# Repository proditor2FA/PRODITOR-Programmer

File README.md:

# PRODITOR-Programmer

https://www.proditor.de

Programmer to flash the HOTP firmware and set the HEX secret build with [KiCAD](https://www.kicad.org/) [free-DAP](https://github.com/ataradov/free-dap) and [openOCD](https://openocd.org/).

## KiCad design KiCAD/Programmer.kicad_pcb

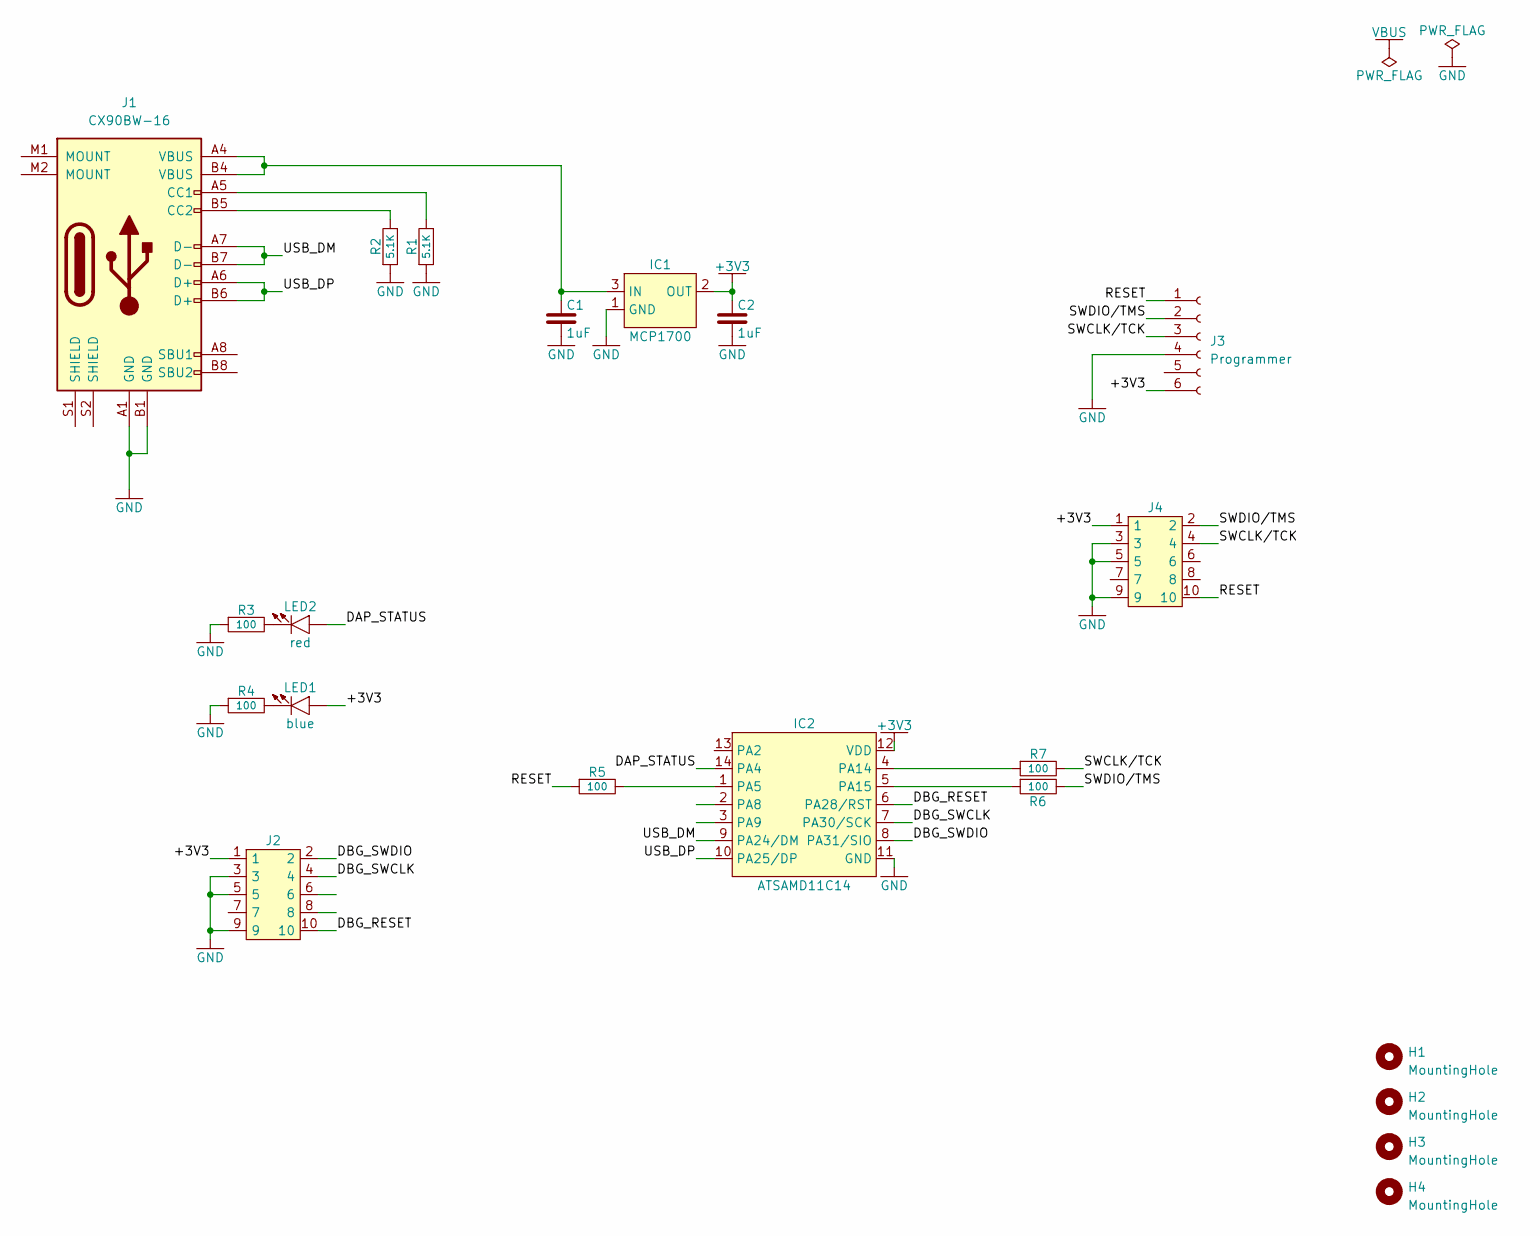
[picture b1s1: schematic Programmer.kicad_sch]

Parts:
C1, C2: 1uF; R_0603_1608Metric_Pad0.98x0.95mm_HandSolder
H1, H2, H3, H4: MountingHole; MountingHole_3.2mm_M3
IC1: MCP1700; SOT-23
IC2: ATSAMD11C14; SOIC-14_3.9x8.7mm_P1.27mm
J1: CX90BW-16; CX90BW-16P
J2, J4: Conn-5x2; Debug_2x05_P1.27mm_Vertical
J3: Programmer; PinHeader_1x06_P1.27mm_Vertical
LED1: blue; R_0603_1608Metric_Pad0.98x0.95mm_HandSolder
LED2: red; R_0603_1608Metric_Pad0.98x0.95mm_HandSolder
R1, R2: 5.1K; R_0603_1608Metric_Pad0.98x0.95mm_HandSolder
R3, R4, R5, R6, R7: 100; R_0603_1608Metric_Pad0.98x0.95mm_HandSolder

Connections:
+3V3: C2.2, IC1.2 (OUT), IC2.12 (VDD), J2.1, J3.6, J4.1, LED1.1 (A)
/DAP_STATUS: IC2.14 (PA4), LED2.1 (A)
/DBG_RESET: IC2.6 (PA28/RST), J2.10
/DBG_SWCLK: IC2.7 (PA30/SCK), J2.4
/DBG_SWDIO: IC2.8 (PA31/SIO), J2.2
/RESET: J3.1, J4.10, R5.1
/SWCLK/TCK: J3.3, J4.4, R7.2
/SWDIO/TMS: J3.2, J4.2, R6.2
/USB_DM: IC2.9 (PA24/DM), J1.A7 (D-), J1.B7 (D-)
/USB_DP: IC2.10 (PA25/DP), J1.A6 (D+), J1.B6 (D+)
GND: C1.1, C2.1, IC1.1 (GND), IC2.11 (GND), J1.A1 (GND), J1.B1 (GND), J2.3, J2.5, J2.9, J3.4, J4.3, J4.5, J4.9, R1.1, R2.1, R3.1, R4.1
unnamed: C1.2, IC1.3 (IN), J1.A4 (VBUS), J1.B4 (VBUS)
unnamed: IC2.1 (PA5), R5.2
unnamed: IC2.4 (PA14), R7.1
unnamed: IC2.5 (PA15), R6.1
unnamed: J1.A5 (CC1), R1.2
unnamed: J1.B5 (CC2), R2.2
unnamed: LED1.2 (K), R4.2
unnamed: LED2.2 (K), R3.2

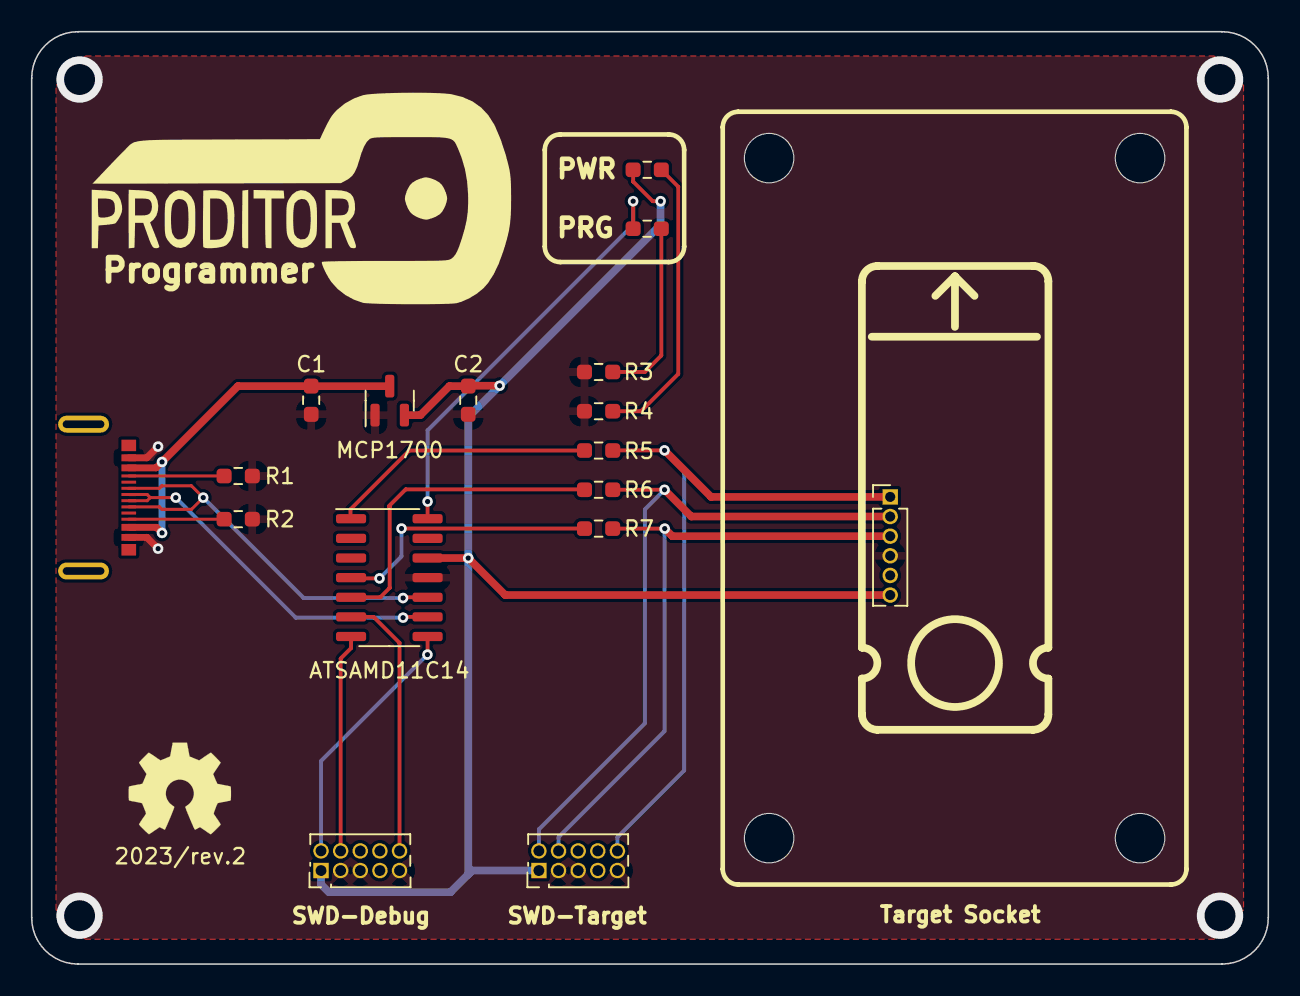
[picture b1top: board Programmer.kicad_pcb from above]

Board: 2 copper layers, 80.0 x 60.3 mm, 21 parts (0 on the bottom side), 19 nets.

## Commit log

2023-09-08 initial push
